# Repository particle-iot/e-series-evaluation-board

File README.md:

# e-series-evaluation-board
Hardware repository for the E series evaluation board

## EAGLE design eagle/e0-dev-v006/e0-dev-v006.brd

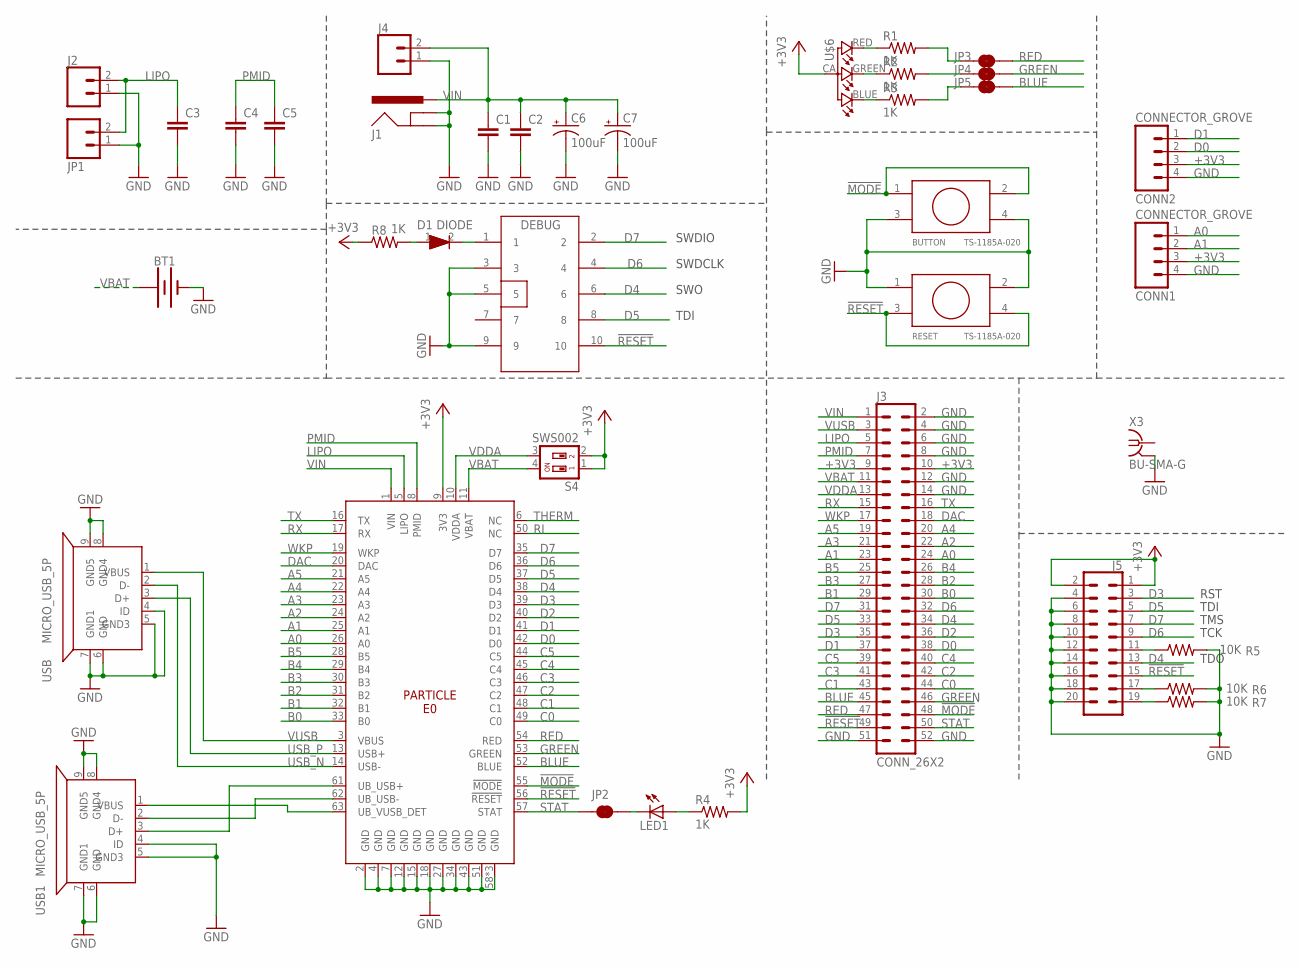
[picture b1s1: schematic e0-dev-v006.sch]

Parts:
BT1: BATTERY-20MM_SMD; BATTCON_20MM
BUTTON: TS-1185A-020
C1, C2, C3, C4, C5: C-EUC0805; C0805
C6, C7: 100uF; PANASONIC_D
CONN1, CONN2: CONNECTOR_GROVE; CONNCTOR_GROVE
D1: DIODE; SOD-323
DEBUG: CON5X2; CON5X2_1.27
J1: POWER_JACKSLT; POWER_JACK_SLOT
J2, J4: CONN_021X02_NO_SILK; 1X02_NO_SILK
J3: CONN_26X2; 2X26
J5: CONN_10X2NOSILK; 2X10_NOSILK
JP1: M02-JST-2MM-SMT; JST-2-SMD@1
JP2, JP3, JP4, JP5: JUMPER-SMT_2_NC_TRACE_NO-SILK; SMT-JUMPER_2_NC_TRACE_NO-SILK
LED1: LED0603; LED-0603
R1, R2, R3, R4, R8: 1K; R0603
R5, R6, R7: 10K; R0603
RESET: TS-1185A-020
S4: SWS002; SMS-002
U1: E0_V005; E0
U$6: RGB-LED-CLMVB-FKARGB; PLCC4-2MM-RGB
USB, USB1: MICRO_USB_5P; MICRO_USB
X3: BU-SMA-G

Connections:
!MODE: BUTTON.1, BUTTON.2, J3.48, U1.55 (!MODE)
!RESET: DEBUG.10, J3.49, J5.15, RESET.3, RESET.4, U1.56 (!RESET)
+3V3: CONN1.3, CONN2.3, J3.9, J3.10, J5.1, J5.2, R4.2, R8.1, S4.1, S4.2, U1.9 (3V3), U$6.CA (1)
A0: CONN1.1, J3.24, U1.26 (A0)
A1: CONN1.2, J3.23, U1.25 (A1)
A2: J3.22, U1.24 (A2)
A3: J3.21, U1.23 (A3)
A4: J3.20, U1.22 (A4)
A5: J3.19, U1.21 (A5)
B0: J3.30, U1.33 (B0)
B1: J3.29, U1.32 (B1)
B2: J3.28, U1.31 (B2)
B3: J3.27, U1.30 (B3)
B4: J3.26, U1.29 (B4)
B5: J3.25, U1.28 (B5)
BLUE: J3.45, JP5.2, U1.52 (BLUE)
C0: J3.44, U1.49 (C0)
C1: J3.43, U1.48 (C1)
C2: J3.42, U1.47 (C2)
C3: J3.41, U1.46 (C3)
C4: J3.40, U1.45 (C4)
C5: J3.39, U1.44 (C5)
D0: CONN2.2, J3.38, U1.42 (D0)
D1: CONN2.1, J3.37, U1.41 (D1)
D2: J3.36, U1.40 (D2)
D3: J3.35, J5.3, U1.39 (D3)
D4: DEBUG.6, J3.34, J5.13, U1.38 (D4)
D5: DEBUG.8, J3.33, J5.5, U1.37 (D5)
D6: DEBUG.4, J3.32, J5.9, U1.36 (D6)
D7: DEBUG.2, J3.31, J5.7, U1.35 (D7)
DAC: J3.18, U1.20 (DAC)
GND: BT1.2 (-), BUTTON.3, BUTTON.4, C1.2, C2.2, C3.2, C4.2, C5.2, C6.-, C7.-, CONN1.4, CONN2.4, DEBUG.3, DEBUG.5, DEBUG.9, J1.GND@1 (GNDBREAK), J1.GND@2 (GND), J2.1, J3.2, J3.4, J3.6, J3.8, J3.12, J3.14, J3.51, J3.52, J4.1, J5.4, J5.6, J5.8, J5.10, J5.12, J5.14, J5.16, J5.18, J5.20, JP1.1 (2), R5.2, R6.2, R7.2, RESET.1, RESET.2, U1.2 (GND), U1.4 (GND), U1.7 (GND), U1.12 (GND), U1.15 (GND), U1.18 (GND), U1.27 (GND), U1.34 (GND), U1.43 (GND), U1.51 (GND), U1.58 (GND), U1.59 (GND), U1.60 (GND), USB.4 (ID), USB.5 (GND3), USB.6 (GND), USB.7 (GND1), USB.8 (GND4), USB.9 (GND5), USB1.4 (ID), USB1.5 (GND3), USB1.6 (GND), USB1.7 (GND1), USB1.8 (GND4), USB1.9 (GND5), X3.2, X3.3 (2), X3.4 (2), X3.5 (2)
GREEN: J3.46, JP4.2, U1.53 (GREEN)
LIPO: C3.1, J2.2, J3.5, JP1.2 (1), U1.5 (LIPO)
unnamed: R1.1, U$6.RED (4)
unnamed: R2.1, U$6.GREEN (3)
unnamed: R3.1, U$6.BLUE (2)
unnamed: U1.63 (UB_VUSB_DET), USB1.1 (VBUS)
unnamed: JP4.1, R2.2
unnamed: JP3.1, R1.2
unnamed: JP5.1, R3.2
unnamed: LED1.A, R4.1
unnamed: J5.11, R5.1
unnamed: J5.17, R6.1
unnamed: J5.19, R7.1
unnamed: JP2.2, LED1.C
unnamed: D1.1, R8.2
unnamed: D1.2, DEBUG.1
PMID: C4.1, C5.1, J3.7, U1.8 (PMID)
RED: J3.47, JP3.2, U1.54 (RED)
RI: U1.50 (NC)
RX: J3.15, U1.17 (RX)
STAT: J3.50, JP2.1, U1.57 (STAT)
THERM: U1.6 (NC)
TX: J3.16, U1.16 (TX)
UB_USB_N: U1.62 (UB_USB-), USB1.2 (D-)
UB_USB_P: U1.61 (UB_USB+), USB1.3 (D+)
USB_N: U1.14 (USB-), USB.2 (D-)
USB_P: U1.13 (USB+), USB.3 (D+)
VBAT: BT1.1 (+), J3.11, S4.4, U1.11 (VBAT)
VDDA: J3.13, S4.3, U1.10 (VDDA)
VIN: C1.1, C2.1, C6.+, C7.+, J1.PWR, J3.1, J4.2, U1.1 (VIN)
VUSB: J3.3, U1.3 (VBUS), USB.1 (VBUS)
WKP: J3.17, U1.19 (WKP)

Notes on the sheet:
TMS
TCK
TDI
TDO
RST
SWO
SWDCLK
SWDIO

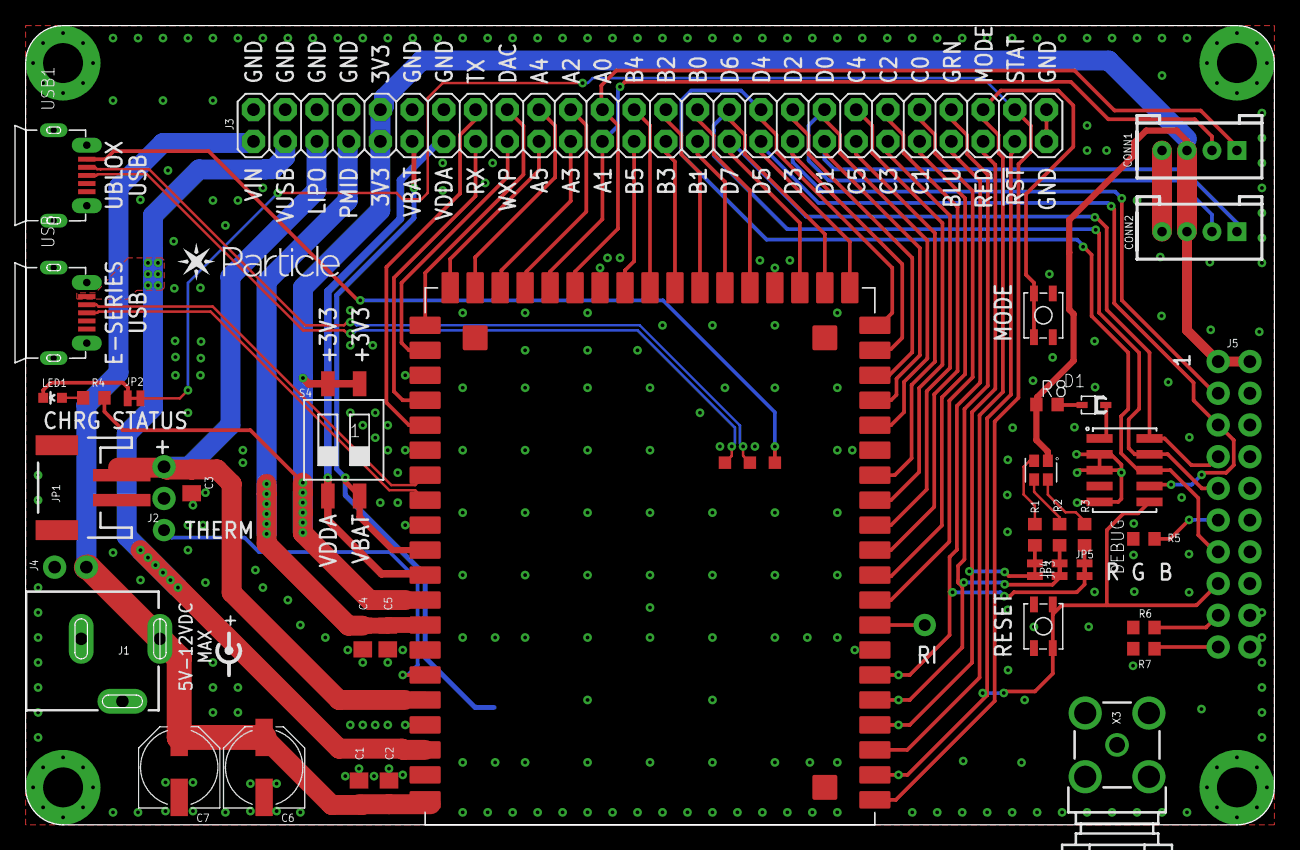
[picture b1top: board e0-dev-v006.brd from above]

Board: 4 copper layers, 100.0 x 64.0 mm, 39 parts (1 on the bottom side), 62 nets.

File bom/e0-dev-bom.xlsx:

IDENTIFIER | DESCRIPTION | VALUE | V | A | W | TOL | PACKAGE ID | DESIGNATOR | QTY | MANUFACTURER | MANUFACTURER P/N | NOTES
BUTTON | SWITCH TACTILE SPST-NO 0.05A 12V | MOMENTARY-SWITCH-SPST-SMD-5.2MM | 12V | 0.05 |  |  | SMD 5.2MM | S1, S2 | 2 | Kingtek | TS4415-250GF | SAME OR EQUIVALENT
CAPACITOR | CAPACITOR | 10uF X5R LOW ESR | 25V |  |  | 0.1 | 805 | C1, C2, C3, C4, C5 | 5 | PANASONIC |  | DO NOT POPULATE
CAPACITOR | SMD ELECTROLYTIC CAPACITOR | 100uF | 25V |  |  | 0.1 |  | C6, C7 | 2 | PANASONIC |  | DO NOT POPULATE
CONNECTOR | LIPO BATTERY CONNECTOR |  |  |  |  |  | JST-2-SMD | JP1 | 1 | KAWEEI | CW2001-02T1-H01-D
CONNECTOR | MICRO USB CONNECTOR |  |  |  |  |  |  | X1, X2 | 2 | KAWEEI | CMCUSB-5BFM14X-01-X
CONNECTOR | SMA TO UFL ADAPTOR |  |  |  |  |  | THROUGH HOLE SMA TO UFL | X3 | 1 | KAWEEI | P1163-0140R | DO NOT POPULATE
CONNECTOR | CONNECTOR_GROVE | GROVE CONNECTOR |  |  |  |  | GROVE 4 PIN THROUGH HOLE | CONN1, CONN2 | 2 | KAWEEI | CW-A2008-04 | SAME OR EQUIVALENT
CONNECTOR | 26X2 FEMALE HEADER, 0.1" PITCH | 26X2 FEMALE HEADER, 0.1" PITCH |  |  |  |  | 0.1" PITCH 26X2 | J3 | 1 | KAWEEI | CS25402-52G-S85-A
CONNECTOR | DC BARREL JACK | POWER_JACKSLT |  |  |  |  | POWER_JACK_SLOT | J1 | 1 | KAWEEI | TDC-005B-20
LED | LED | RED LED |  |  |  |  | 603 | LED1 | 1 | EVERLIGHT | 19-217/R6C-AL1M2VY/3T
LED | RGB-LED-CLMVB-FKARGB | RGB LED |  |  |  |  | 4-PLCC (3.2 mm x 2.8mm) | U$6 | 1 | CREE | CLMVB-FKA-CFHEHLCBB7A363
RESISTOR | RESISTOR | 10K |  |  |  | 0.05 | 603 | R5, R6, R7 | 3 | Uniohm | RS-03K103JT
RESISTOR | RESISTOR | 1K |  |  |  | 0.05 | 603 | R1, R2, R3, R4 | 4 | Unihom | RS-03K102JT
SLIDE SWITCH | SWITCH SLIDE DIP SPST 100MA 20V | SLIDE SWITCH |  |  |  |  |  | S4 | 1 | Kingtek | DSIC0TSGET | SAME OR EQUIVALENT

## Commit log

2018-01-30 Added bom and gerber files
2021-02-23 Add eval board v006

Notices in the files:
parts and their libraries:
SparkFun-Jumpers: Licensing: Creative Commons ShareAlike 4.0 International - https://creativecommons.org/licenses/by-sa/4.0
